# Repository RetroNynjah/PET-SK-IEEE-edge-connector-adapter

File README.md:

# PET SK IEEE-488 to edge connector adapter

Many accessories for the CBM PET such as SD2PET and PETdisk are desgined for models which have an edge connector for IEEE-BUS while the PET 8032-SK/8096-SK/200 has a standard IEEE-488 connector. That's a D-shaped connector which is sometimes called GPIB connector or Centronix connector.  
This cheap adapter converts from the standard IEEE-488 port on the SK models to a card edge so that standard PET accessories with edge connectors can be used.  

<br/>

The adapter is very simple. It has straight connections from one side to the other. The part count can't get much lower as it only contains one component except for the PCB, a male right-angled IEEE-488 connector.  
Example of suitable connector: https://www.aliexpress.com/item/32795413098.html

| **Signal** | **GPIB** | **Edge** |
|:----------:|:--------:|:--------:|
|    DIO1    |     1    |     1    |
|    DIO2    |     2    |     2    |
|    DIO3    |     3    |     3    |
|    DIO4    |     4    |     4    |
|    EOI     |     5    |     5    |
|    DAV     |     6    |     6    |
|    NRFD    |     7    |     7    |
|    NDAC    |     8    |     8    |
|    IFC     |     9    |     9    |
|    SRQ     |     10   |     10   |
|    ATN     |     11   |     11   |
|   SHIELD   |     12   |     12   |
|    DIO5    |     13   |     A    |
|    DIO6    |     14   |     B    |
|    DIO7    |     15   |     C    |
|    DIO8    |     16   |     D    |
|    REN     |     17   |     E    |
|    GND     |     18   |     F    |
|    GND     |     19   |     H    |
|    GND     |     20   |     J    |
|    GND     |     21   |     K    |
|    GND     |     22   |     L    |
|    GND     |     23   |     M    |
|    GND     |     24   |     N    |

<br/>
PETdisk Max v2 installed in PET

<br/>
PETdisk Max v2 installed together with floppy drive in PET

Thanks to Jonas for the PETdisk Max v2 photos.

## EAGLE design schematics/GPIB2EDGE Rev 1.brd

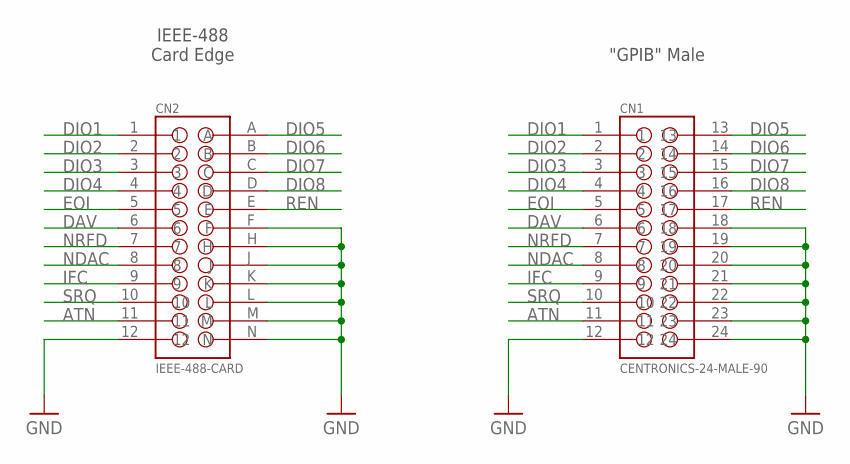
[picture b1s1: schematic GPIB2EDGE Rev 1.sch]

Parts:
CN1: CENTRONICS-24-MALE-90; CENTRONICS-24-M-90
CN2: IEEE-488-CARD; IEEE-488-EDGE-CARD

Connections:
ATN: CN1.11, CN2.11
DAV: CN1.6, CN2.6
DIO1: CN1.1, CN2.1
DIO2: CN1.2, CN2.2
DIO3: CN1.3, CN2.3
DIO4: CN1.4, CN2.4
DIO5: CN1.13, CN2.A
DIO6: CN1.14, CN2.B
DIO7: CN1.15, CN2.C
DIO8: CN1.16, CN2.D
EOI: CN1.5, CN2.5
GND: CN1.12, CN1.18, CN1.19, CN1.20, CN1.21, CN1.22, CN1.23, CN1.24, CN2.12, CN2.F, CN2.H, CN2.J, CN2.K, CN2.L, CN2.M, CN2.N
IFC: CN1.9, CN2.9
NDAC: CN1.8, CN2.8
NRFD: CN1.7, CN2.7
REN: CN1.17, CN2.E
SRQ: CN1.10, CN2.10

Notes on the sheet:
IEEE-488 Card Edge
"GPIB" Male

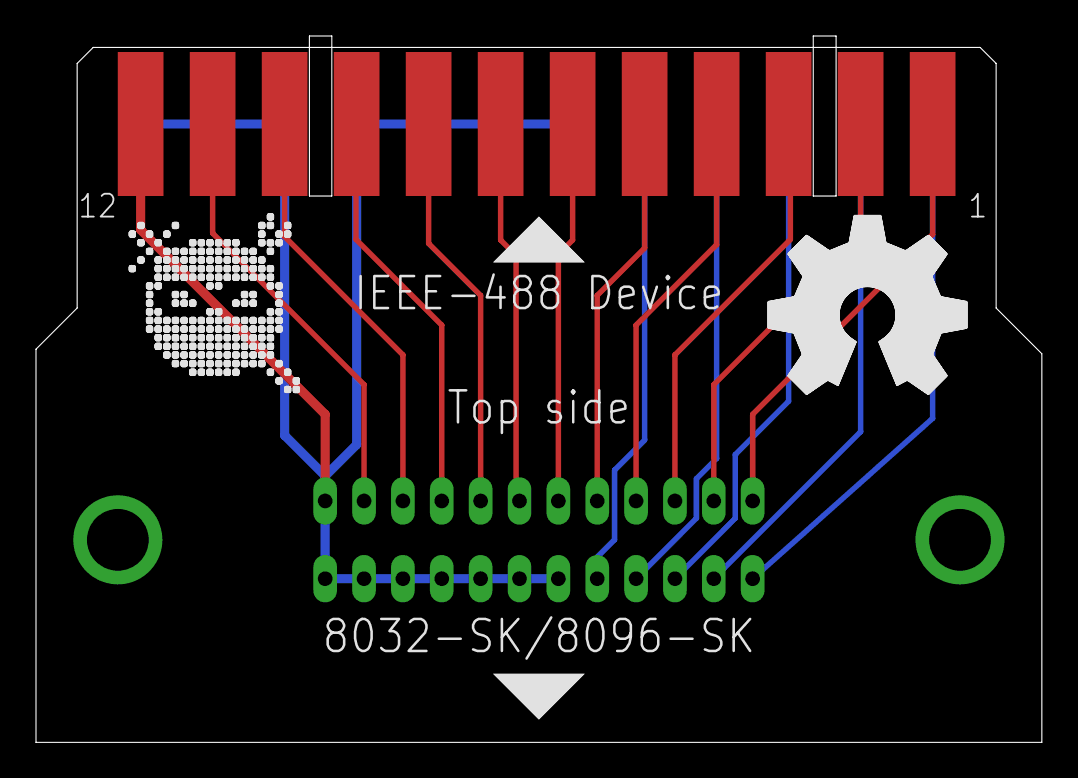
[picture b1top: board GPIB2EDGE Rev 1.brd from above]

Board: 2 copper layers, 55.9 x 39.2 mm, 4 parts (1 on the bottom side), 17 nets.

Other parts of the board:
U$1: OSHW_NOTEXT_10MM
U$2: RETRONINJA_NOTEXT_10MM

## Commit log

2023-10-01 Initial upload
